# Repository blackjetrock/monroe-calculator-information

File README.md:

# Monroe Calculator Information

Information on Monroe and Litton Monroe calculators

Monroe Classmate 88

Monroe 2890

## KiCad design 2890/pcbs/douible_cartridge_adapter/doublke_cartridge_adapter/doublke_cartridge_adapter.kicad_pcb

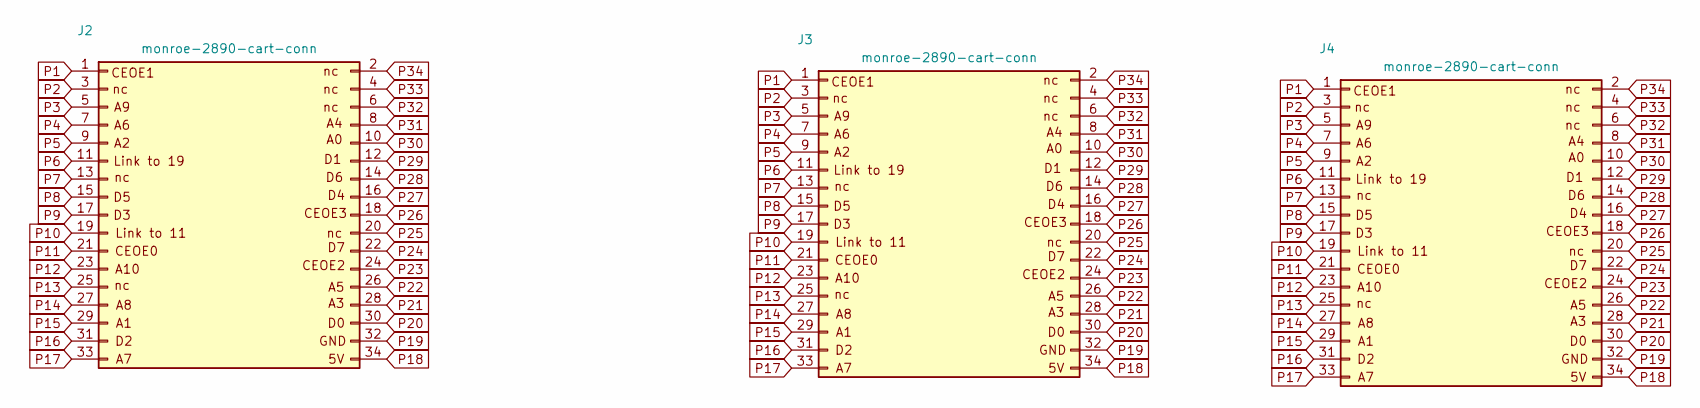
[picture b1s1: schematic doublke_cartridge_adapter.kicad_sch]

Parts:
J2: monroe-2890-cart-conn; monroe-2890-cartridge-edge
J3, J4: monroe-2890-cart-conn; monroe-2890-edge-connector

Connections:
P1: J2.1, J3.1, J4.1
P2: J2.3, J3.3, J4.3
P3: J2.5, J3.5, J4.5
P4: J2.7, J3.7, J4.7
P5: J2.9, J3.9, J4.9
P6: J2.11, J3.11, J4.11
P7: J2.13, J3.13, J4.13
P8: J2.15, J3.15, J4.15
P9: J2.17, J3.17, J4.17
P10: J2.19, J3.19, J4.19
P11: J2.21, J3.21, J4.21
P12: J2.23, J3.23, J4.23
P13: J2.25, J3.25, J4.25
P14: J2.27, J3.27, J4.27
P15: J2.29, J3.29, J4.29
P16: J2.31, J3.31, J4.31
P17: J2.33, J3.33, J4.33
P18: J2.34, J3.34, J4.34
P19: J2.32, J3.32, J4.32
P20: J2.30, J3.30, J4.30
P21: J2.28, J3.28, J4.28
P22: J2.26, J3.26, J4.26
P23: J2.24, J3.24, J4.24
P24: J2.22, J3.22, J4.22
P25: J2.20, J3.20, J4.20
P26: J2.18, J3.18, J4.18
P27: J2.16, J3.16, J4.16
P28: J2.14, J3.14, J4.14
P29: J2.12, J3.12, J4.12
P30: J2.10, J3.10, J4.10
P31: J2.8, J3.8, J4.8
P32: J2.6, J3.6, J4.6
P33: J2.4, J3.4, J4.4
P34: J2.2, J3.2, J4.2

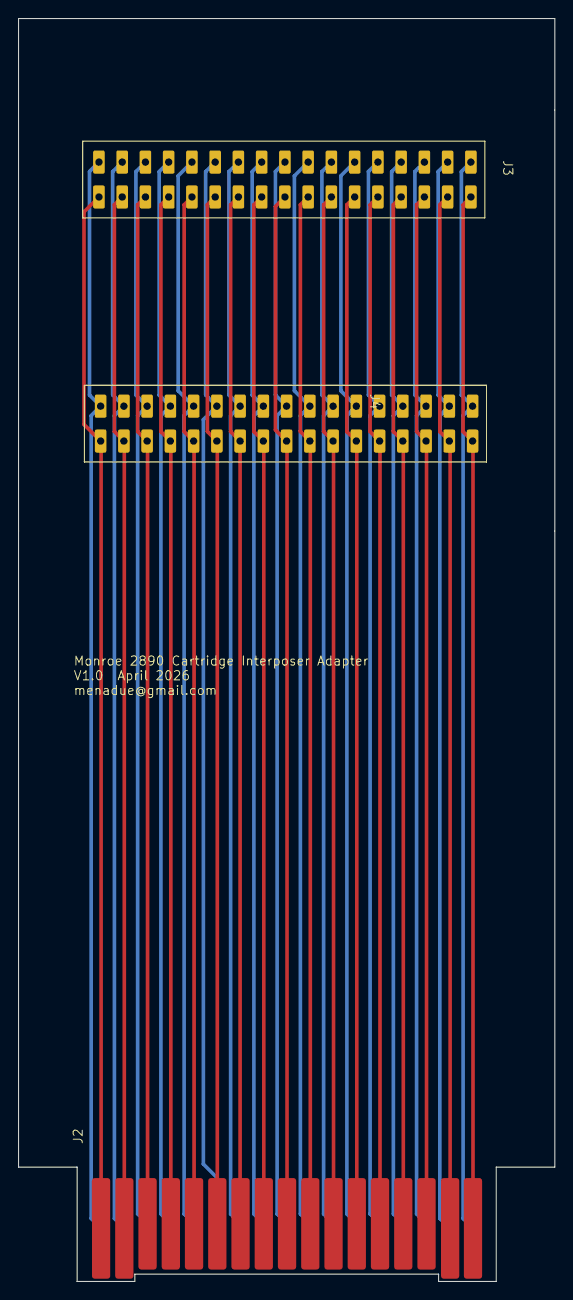
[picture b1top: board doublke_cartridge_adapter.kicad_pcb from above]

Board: 2 copper layers, 58.6 x 138.0 mm, 3 parts (0 on the bottom side), 34 nets.

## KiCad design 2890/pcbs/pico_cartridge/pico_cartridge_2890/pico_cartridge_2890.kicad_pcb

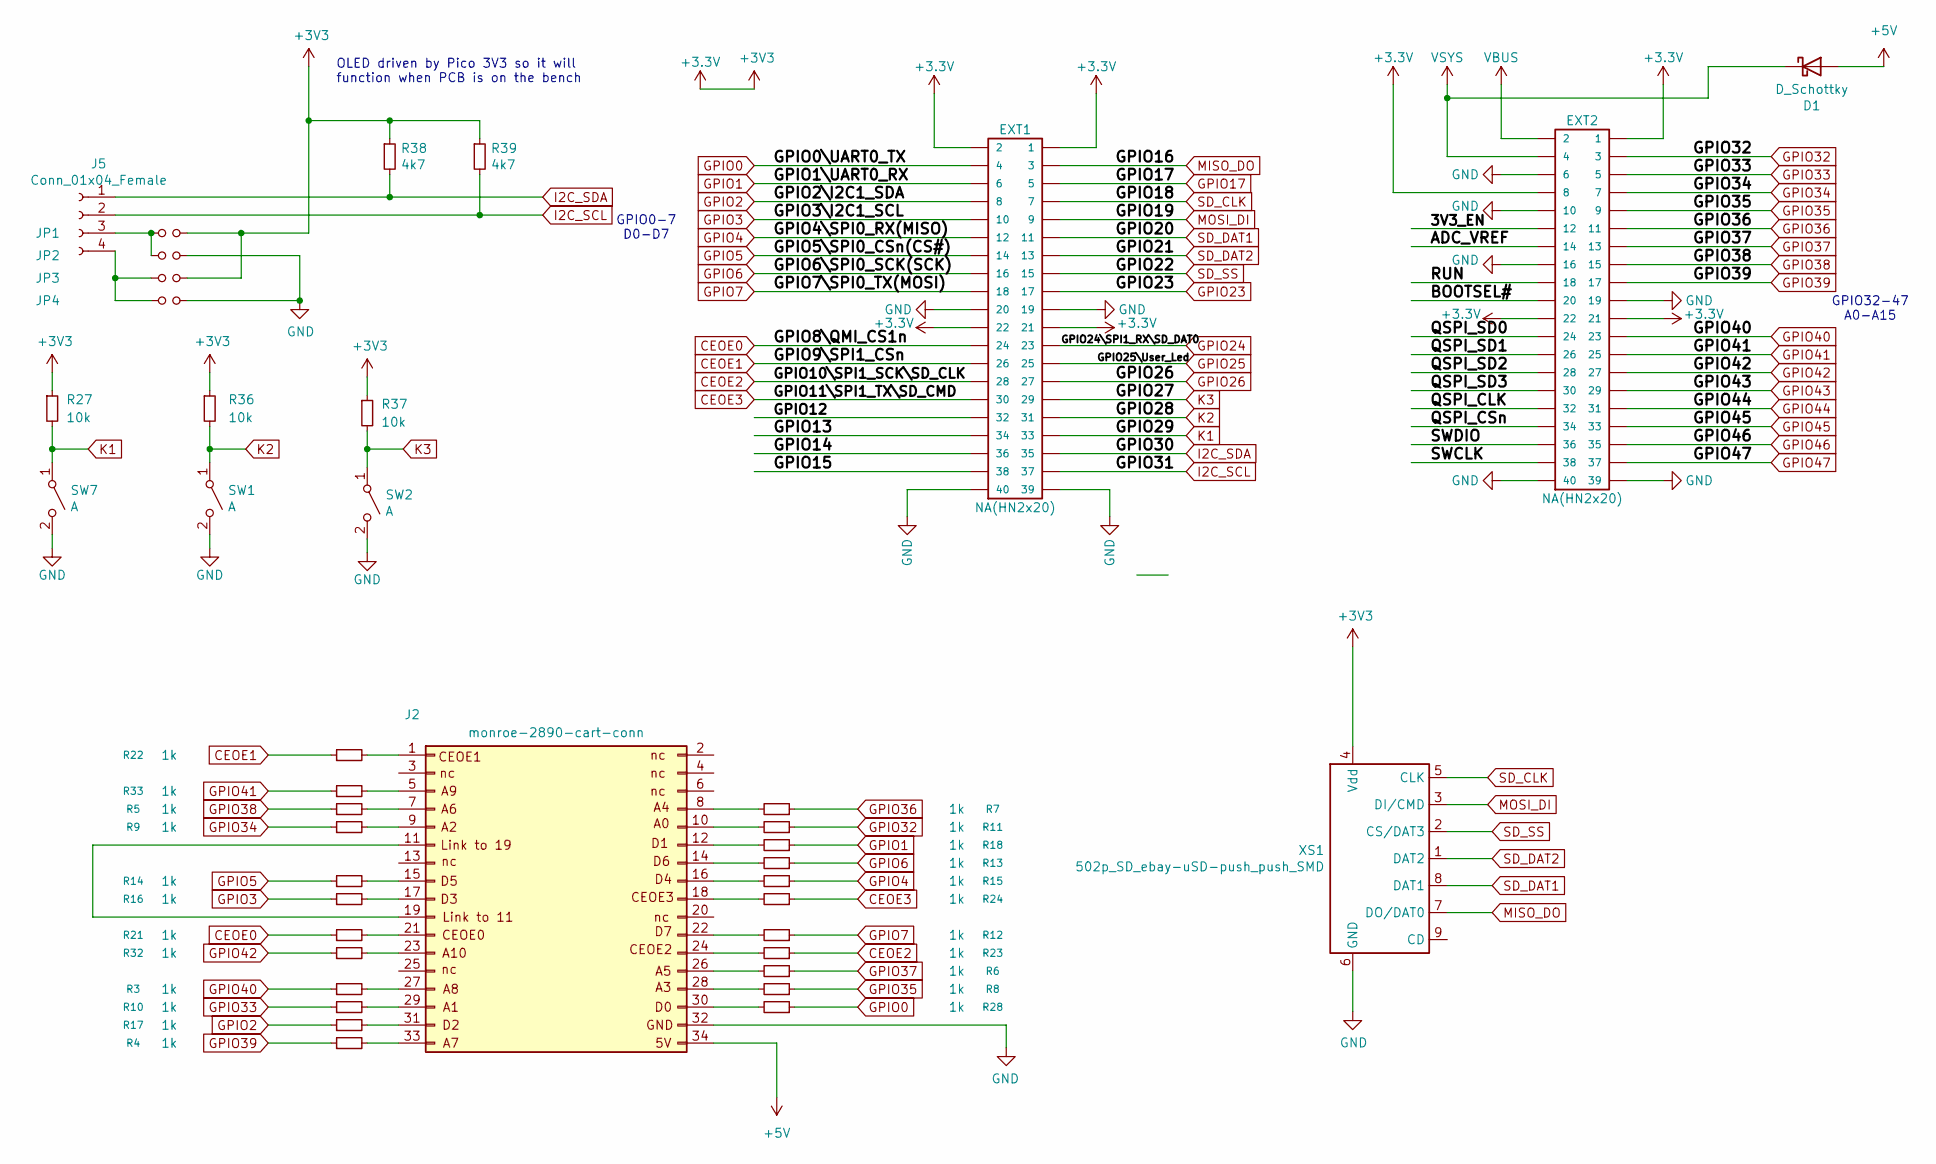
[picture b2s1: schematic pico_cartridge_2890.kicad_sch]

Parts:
D1: D_Schottky; D_SOD-123
EXT1, EXT2: NA(HN2x20); PinSocket_2x20_P2.54mm_Vertical
J2: monroe-2890-cart-conn; monroe-2890-cartridge-edge
J5: Conn_01x04_Female; PinHeader_1x04_P2.54mm_Vertical
JP1, JP2, JP3, JP4: Jumper_NO_Small; SolderJumper-2_P1.3mm_Open_TrianglePad1.0x1.5mm
R3, R4, R5, R6, R7, R8, R9, R10, R11, R12, R13, R14, R15, R16, R17, R18, R21, R22, R23, R24, R28, R32, R33: 1k; R_0805_2012Metric_Pad1.20x1.40mm_HandSolder
R27, R36, R37: 10k; R_0805_2012Metric
R38, R39: 4k7; R_0805_2012Metric_Pad1.20x1.40mm_HandSolder
SW1, SW2, SW7: A; SW_PUSH_6mm
XS1: 502p_SD_ebay-uSD-push_push_SMD; Conn_uSDcard

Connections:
+3.3V: EXT1.1, EXT1.2, EXT1.21, EXT1.22, EXT2.1, EXT2.8, EXT2.21, EXT2.22, JP1.2, JP3.2, R27.1, R36.1, R37.1, R38.1, R39.1, XS1.4 (Vdd)
+5V: D1.2 (A), J2.34
/3V3_EN: EXT2.12
/ADC_VREF: EXT2.14
/BOOTSEL#: EXT2.20
/GPIO12: EXT1.32
/GPIO13: EXT1.34
/GPIO14: EXT1.36
/GPIO15: EXT1.38
/QSPI_CLK: EXT2.32
/QSPI_CSn: EXT2.34
/QSPI_SD0: EXT2.24
/QSPI_SD1: EXT2.26
/QSPI_SD2: EXT2.28
/QSPI_SD3: EXT2.30
/RUN: EXT2.18
/SWCLK: EXT2.38
/SWDIO: EXT2.36
CEOE0: EXT1.24, R21.1
CEOE1: EXT1.26, R22.1
CEOE2: EXT1.28, R23.1
CEOE3: EXT1.30, R24.1
GND: EXT1.19, EXT1.20, EXT1.39, EXT1.40, EXT2.6, EXT2.10, EXT2.16, EXT2.19, EXT2.39, EXT2.40, J2.32, JP2.2, JP4.2, SW1.2 (B), SW2.2 (B), SW7.2 (B), XS1.6 (GND)
GPIO0: EXT1.4, R28.1
GPIO1: EXT1.6, R18.1
GPIO2: EXT1.8, R17.1
GPIO3: EXT1.10, R16.1
GPIO4: EXT1.12, R15.1
GPIO5: EXT1.14, R14.1
GPIO6: EXT1.16, R13.1
GPIO7: EXT1.18, R12.1
GPIO17: EXT1.5
GPIO23: EXT1.17
GPIO24: EXT1.23
GPIO25: EXT1.25
GPIO26: EXT1.27
GPIO32: EXT2.3, R11.1
GPIO33: EXT2.5, R10.1
GPIO34: EXT2.7, R9.1
GPIO35: EXT2.9, R8.1
GPIO36: EXT2.11, R7.1
GPIO37: EXT2.13, R6.1
GPIO38: EXT2.15, R5.1
GPIO39: EXT2.17, R4.1
GPIO40: EXT2.23, R3.1
GPIO41: EXT2.25, R33.1
GPIO42: EXT2.27, R32.1
GPIO43: EXT2.29
GPIO44: EXT2.31
GPIO45: EXT2.33
GPIO46: EXT2.35
GPIO47: EXT2.37
I2C_SCL: EXT1.37, J5.2, R39.2
I2C_SDA: EXT1.35, J5.1, R38.2
K1: EXT1.33, R27.2, SW7.1 (A)
K2: EXT1.31, R36.2, SW1.1 (A)
K3: EXT1.29, R37.2, SW2.1 (A)
MISO_DO: EXT1.3, XS1.7 (DO/DAT0)
MOSI_DI: EXT1.9, XS1.3 (DI/CMD)
unnamed: J2.1, R22.2
unnamed: J2.5, R33.2
unnamed: J2.7, R5.2
unnamed: J2.8, R7.2
unnamed: J2.9, R9.2
unnamed: J2.10, R11.2
unnamed: J2.11, J2.19
unnamed: J2.12, R18.2
unnamed: J2.14, R13.2
unnamed: J2.15, R14.2
unnamed: J2.16, R15.2
unnamed: J2.17, R16.2
unnamed: J2.18, R24.2
unnamed: J2.21, R21.2
unnamed: J2.22, R12.2
unnamed: J2.23, R32.2
unnamed: J2.24, R23.2
unnamed: J2.26, R6.2
unnamed: J2.27, R3.2
unnamed: J2.28, R8.2
unnamed: J2.29, R10.2
unnamed: J2.30, R28.2
unnamed: J2.31, R17.2
unnamed: J2.33, R4.2
unnamed: J5.3, JP1.1, JP2.1
unnamed: J5.4, JP3.1, JP4.1
SD_CLK: EXT1.7, XS1.5 (CLK)
SD_DAT1: EXT1.11, XS1.8 (DAT1)
SD_DAT2: EXT1.13, XS1.1 (DAT2)
SD_SS: EXT1.15, XS1.2 (CS/DAT3)
VBUS: EXT2.2
VSYS: D1.1 (K), EXT2.4

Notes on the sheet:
GPIO32-47 A0-A15
OLED driven by Pico 3V3 so it will function when PCB is on the bench
GPIO0-7 D0-D7

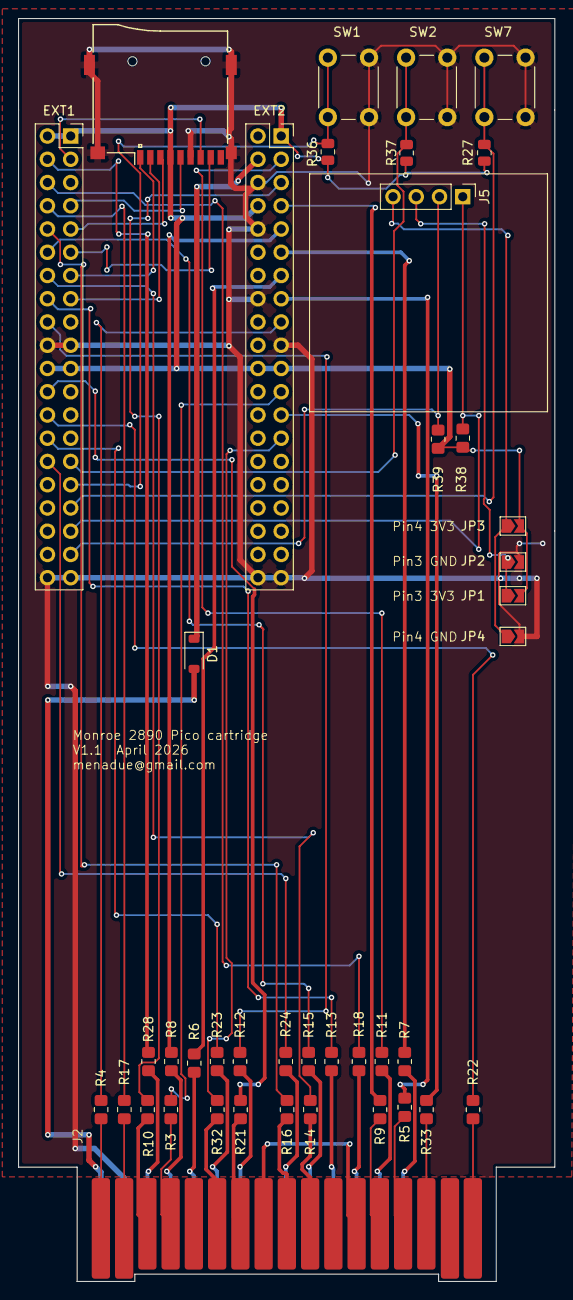
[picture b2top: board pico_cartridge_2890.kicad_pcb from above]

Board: 2 copper layers, 58.6 x 138.0 mm, 41 parts (0 on the bottom side), 64 nets.

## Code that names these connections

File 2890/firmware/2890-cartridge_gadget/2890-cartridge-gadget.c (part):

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// 


#define MASK_CEOE0    (1 << PIN_CEOE0)
#define MASK_CEOE1    (1 << PIN_CEOE1)
#define MASK_CEOE2    (1 << PIN_CEOE2)
#define MASK_CEOE3    (1 << PIN_CEOE3)

#define VAL_CEOE0_LOW (             MASK_CEOE1 | MASK_CEOE2 | MASK_CEOE3)
#define VAL_CEOE1_LOW (MASK_CEOE0 |              MASK_CEOE2 | MASK_CEOE3)
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const int PIN_D6        =  6;
const int PIN_D7        =  7;

const int PIN_CEOE0     =  8;
const int PIN_CEOE1     =  9;
const int PIN_CEOE2     =  10;
const int PIN_CEOE3     =  11;

const int PIN_NRDS      =  12;
const int PIN_SYNC      =  13;
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  //set_gpio_input(PIN_NRDS);
  //set_gpio_input(PIN_SYNC);
  //set_gpio_input(PIN_PHI2);
  set_gpio_input(PIN_CEOE0);
  set_gpio_input(PIN_CEOE1);
  set_gpio_input(PIN_CEOE2);
  set_gpio_input(PIN_CEOE3);

  // SD card GPIOs here
  set_gpio_input(PIN_K3);
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
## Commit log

2026-03-13 "Update"
2026-03-13 Update README title and add calculator models
2026-03-13 Add images of Monroe calculators to README
    Added images for Monroe Classmate 88 and Monroe 2890.
2026-03-23 Fix formatting and standardize entries in test_modes.txt
2026-03-23 Fix formatting and add new fraction and subtraction tasks
